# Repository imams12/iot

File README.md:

# IOT 
1. IR Schematic, PCB, & 3D
2. Serial communication python to arduino
3. Sensor DHT MQTT to python with MySQL database

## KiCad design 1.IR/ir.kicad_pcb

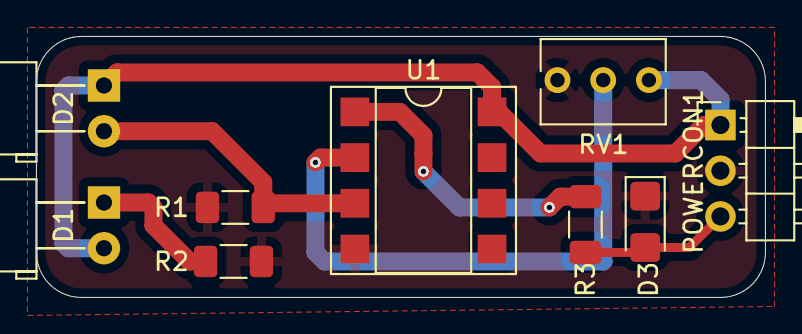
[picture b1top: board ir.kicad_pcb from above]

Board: 2 copper layers, 40.5 x 14.5 mm, 9 parts (0 on the bottom side), 7 nets.

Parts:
D1, D2: LED; LED_D5.0mm_Horizontal_O3.81mm_Z3.0mm
D3: LED; LED_1206_3216Metric_Castellated
POWERCON1: CON_POWER; PinHeader_1x03_P2.54mm_Horizontal
R1: 100; R_1206_3216Metric_Pad1.30x1.75mm_HandSolder
R2: 10K; R_1206_3216Metric_Pad1.30x1.75mm_HandSolder
R3: 330; R_1206_3216Metric_Pad1.30x1.75mm_HandSolder
RV1: 10K; Potentiometer_Bourns_3266Y_Vertical
U1: LM358; DIP-8_W7.62mm_SMDSocket_SmallPads

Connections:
+5V: D1.2 (A), D2.1 (K), POWERCON1.1, RV1.1, U1.8 (V+)
GND: D3.1 (K), POWERCON1.2, R1.2, R2.2, RV1.3, U1.4 (V-)
unnamed: D1.1 (K), R1.1
unnamed: D2.2 (A), R2.1, U1.3 (+)
unnamed: R3.2, U1.1
unnamed: RV1.2, U1.2 (-)
OUT: D3.2 (A), POWERCON1.3, R3.1

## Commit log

2024-04-27 description file
